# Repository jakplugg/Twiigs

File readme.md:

# Twiigs 

### 8hp dual branches.

#### PCB redesign by J. Matheson. 

it works with the same firmware, or run branches on one side, and twigs firmware on the other. all 4 inputs are normaled in a chain.

Preliminary
[Google sheets BOM](https://docs.google.com/spreadsheets/d/1JGUupowo2NgiNVYJbO-taDfZpJ7LFIUUvPUNU3bPbuE/edit#gid=1149505224)

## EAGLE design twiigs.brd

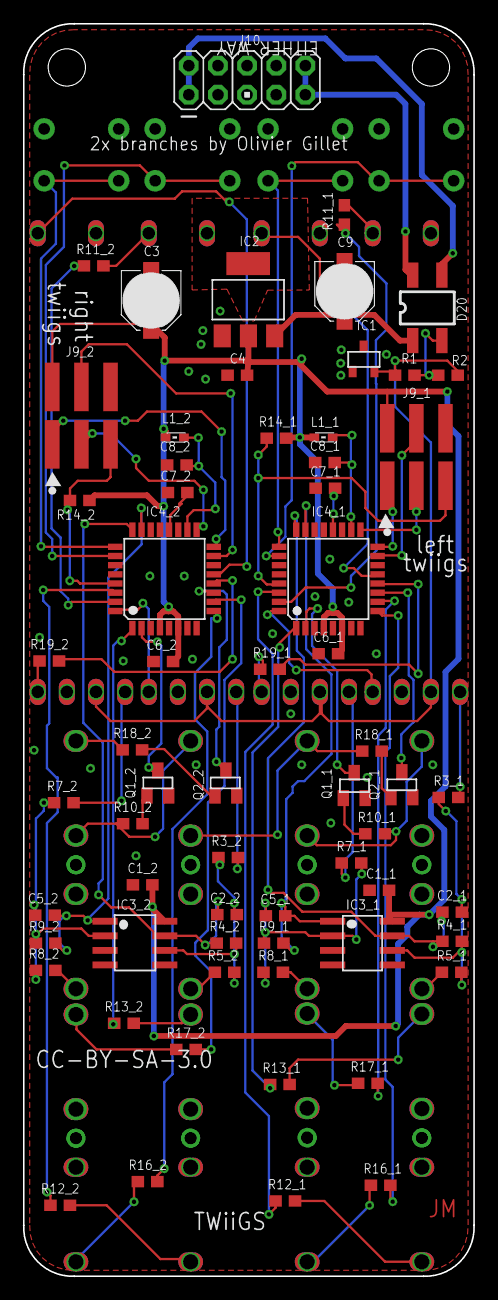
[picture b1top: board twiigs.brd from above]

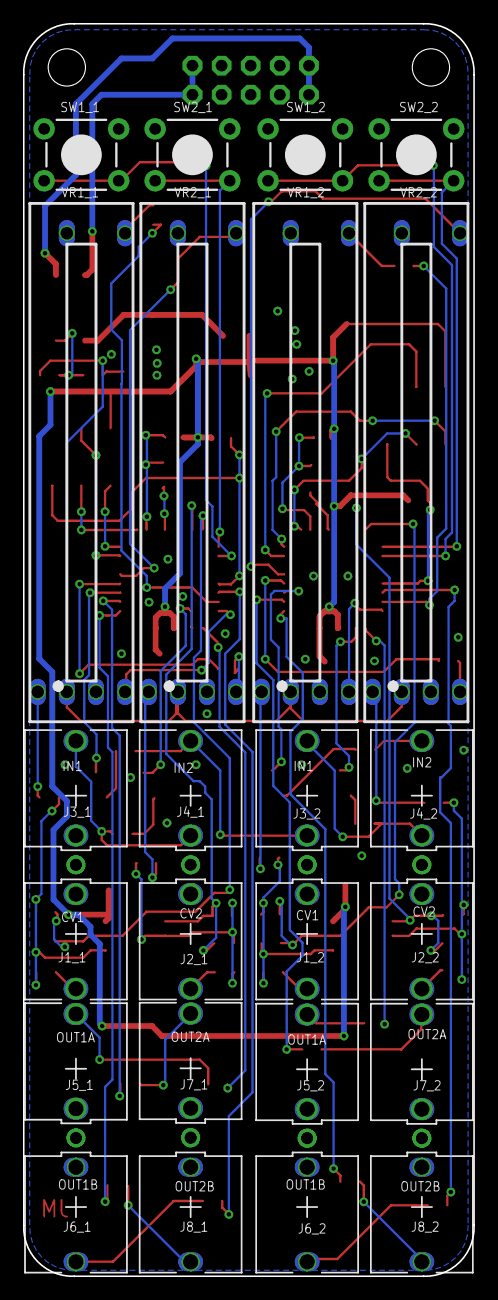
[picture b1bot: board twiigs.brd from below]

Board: 2 copper layers, 39.3 x 109.2 mm, 87 parts (24 on the bottom side), 79 nets.

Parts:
C1_1: 100n; CAP_0603_C1_1
C1_2: 100n; CAP_0603_C1_2
C2_1: 1n; CAP_0603_C2_1
C2_2: 1n; CAP_0603_C2_2
C3: 22u; PANASONIC_C
C4: 100n; CAP_0603
C5_1: 1n; CAP_0603_C5_1
C5_2: 1n; CAP_0603_C5_2
C6_1: 100n; CAP_0603_C6_1
C6_2: 100n; CAP_0603_C6_2
C7_1: 100n; CAP_0603_C7_1
C7_2: 100n; CAP_0603_C7_2
C8_1: 100n; CAP_0603_C8_1
C8_2: 100n; CAP_0603_C8_2
C9: 22u; PANASONIC_C_C9
D20: MB1S; SOP-4/6.5x2.54
IC1: LM4040 5.0V; DBZ_R-PDSO-G3
IC2: LM1117-5.0; SOT223
IC3_1: MCP6002; SO08
IC3_2: MCP6002; SO08_IC3_2
IC4_1: ATMEGA88PA-AU; TQFP32-08
IC4_2: ATMEGA88PA-AU; TQFP32-08_IC4_2
J1_1: CV1; Thonkiconn
J1_2: CV1; Thonkiconn_J1_2
J2_1: CV2; Thonkiconn_J2_1
J2_2: CV2; Thonkiconn_J2_2
J3_1: IN1; Thonkiconn_J3_1
J3_2: IN1; Thonkiconn_J3_2
J4_1: IN2; Thonkiconn_J4_1
J4_2: IN2; Thonkiconn_J4_2
J5_1: OUT1A; Thonkiconn_J5_1
J5_2: OUT1A; Thonkiconn_J5_2
J6_1: OUT1B; Thonkiconn_J6_1
J6_2: OUT1B; Thonkiconn_J6_2
J7_1: OUT2A; Thonkiconn_J7_1
J7_2: OUT2A; Thonkiconn_J7_2
J8_1: OUT2B; Thonkiconn_J8_1
J8_2: OUT2B; Thonkiconn_J8_2
J9_1: HDR-2x3S/2.54x2.54/Sh15x11
J9_2: HDR-2x3S/2.54x2.54/Sh15x11_J9_2
J10: M05X2PTH; AVR_ICSP
L1_1: 0603
L1_2: 0603_L1_2
Q1_1: MMBT3904; SOT23-BEC
Q1_2: MMBT3904; SOT23-BEC_Q1_2
Q2_1: MMBT3904; SOT23-BEC_Q2_1
Q2_2: MMBT3904; SOT23-BEC_Q2_2
R1: 3.3k; RES_0603
R2: 3.3k; RES_0603_R2
R3_1: 100k; RES_0603_R3_1
R3_2: 100k; RES_0603_R3_2
R4_1: 100k; RES_0603_R4_1
R4_2: 100k; RES_0603_R4_2
R5_1: 100k; RES_0603_R5_1
R5_2: 100k; RES_0603_R5_2
R7_1: 100k; RES_0603_R7_1
R7_2: 100k; RES_0603_R7_2
R8_1: 100k; RES_0603_R8_1
R8_2: 100k; RES_0603_R8_2
R9_1: 100k; RES_0603_R9_1
R9_2: 100k; RES_0603_R9_2
R10_1: 100k; RES_0603_R10_1
R10_2: 100k; RES_0603_R10_2
R11_1: 220; RES_0603_R11_1
R11_2: 220; RES_0603_R11_2
R12_1: 1.0k; RES_0603_R12_1
R12_2: 1.0k; RES_0603_R12_2
R13_1: 1.0k; RES_0603_R13_1
R13_2: 1.0k; RES_0603_R13_2
R14_1: 10k; RES_0603_R14_1
R14_2: 10k; RES_0603_R14_2
R16_1: 1.0k; RES_0603_R16_1
R16_2: 1.0k; RES_0603_R16_2
R17_1: 1.0k; RES_0603_R17_1
R17_2: 1.0k; RES_0603_R17_2
R18_1: 100k; RES_0603_R18_1
R18_2: 100k; RES_0603_R18_2
R19_1: 220; RES_0603_R19_1
R19_2: 220; RES_0603_R19_2
SW1_1: TACTILE-PTH
SW1_2: TACTILE-PTH_SW1_2
SW2_1: TACTILE-PTH_SW2_1
SW2_2: TACTILE-PTH_SW2_2
VR1_1: BOURNS_PTL_30mm
VR1_2: BOURNS_PTL_30mm_VR1_2
VR2_1: BOURNS_PTL_30mm_VR2_1
VR2_2: BOURNS_PTL_30mm_VR2_2

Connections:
+5V: C1_1.1, C1_2.1, C3.+, C4.1, C6_1.1, C6_2.1, IC2.2, IC3_1.8, IC3_2.8, IC4_1.4, IC4_1.6, IC4_2.4, IC4_2.6, J9_1.2, J9_2.2, L1_1.1, L1_2.1, R14_1.2, R14_2.2
AREF_1: C7_1.1, IC4_1.20
AREF_2: C7_2.1, IC4_2.20
GATE1_IN_1: J3_1.2, J4_1.1, R10_1.2
GATE1_IN_2: J3_2.2, J4_2.1, R10_2.2
GATE2_IN_2: J4_2.2, R18_2.2
GND: C1_1.2, C1_2.2, C3.-, C4.2, C6_1.2, C6_2.2, C7_1.2, C7_2.2, C8_1.2, C8_2.2, C9.-, IC1.1, IC2.1, IC3_1.3, IC3_1.4, IC3_1.5, IC3_2.3, IC3_2.4, IC3_2.5, IC4_1.3, IC4_1.5, IC4_1.21, IC4_2.3, IC4_2.5, IC4_2.21, J1_1.3, J1_2.3, J2_1.3, J2_2.3, J3_1.1, J3_1.3, J3_2.3, J4_1.3, J4_2.3, J5_1.3, J5_2.3, J6_1.3, J6_2.3, J7_1.3, J7_2.3, J8_1.3, J8_2.3, J9_1.6, J9_2.6, J10.3, J10.4, J10.5, J10.6, J10.7, J10.8, Q1_1.E, Q1_2.E, Q2_1.E, Q2_2.E, SW1_1.1, SW1_1.2, SW1_2.1, SW1_2.2, SW2_1.1, SW2_1.2, SW2_2.1, SW2_2.2, VR1_1.3, VR1_2.3, VR2_1.3, VR2_2.3
IN1_1: IC4_1.2, Q1_1.C
IN1_2: IC4_2.2, Q1_2.C
IN2_1: IC4_1.11, Q2_1.C
IN2_2: IC4_2.11, Q2_2.C
MISO_1: IC4_1.16, J9_1.1
MISO_2: IC4_2.16, J9_2.1
MOSI_1: IC4_1.15, J9_1.4
MOSI_2: IC4_2.15, J9_2.4
unnamed: Q1_1.B, R10_1.1
unnamed: Q1_2.B, R10_2.1
unnamed: Q2_1.B, R18_1.1
unnamed: Q2_2.B, R18_2.1
unnamed: C5_1.1, IC3_1.2, R7_1.2, R8_1.2, R9_1.1
unnamed: C5_2.1, IC3_2.2, R7_2.2, R8_2.2, R9_2.1
unnamed: J8_1.2, R16_1.2
unnamed: J8_2.2, R16_2.2
unnamed: R7_1.1, VR2_1.2
unnamed: R7_2.1, VR2_2.2
unnamed: R3_1.1, VR1_1.2
unnamed: R3_2.1, VR1_2.2
unnamed: J1_1.2, R5_1.1
unnamed: J1_2.2, R5_2.1
unnamed: J2_1.2, R8_1.1
unnamed: J2_2.2, R8_2.1
unnamed: IC4_1.31, R11_1.1
unnamed: IC4_2.31, R11_2.1
unnamed: R11_1.2, VR1_1.5
unnamed: R11_2.2, VR1_2.5
unnamed: IC4_1.32, VR1_1.6
unnamed: IC4_2.32, VR1_2.6
unnamed: IC4_1.13, VR2_1.5
unnamed: IC4_2.13, VR2_2.5
unnamed: R19_1.1, VR2_1.6
unnamed: R19_2.1, VR2_2.6
unnamed: IC4_1.12, R19_1.2
unnamed: IC4_2.12, R19_2.2
unnamed: C2_1.1, IC3_1.6, R3_1.2, R4_1.1, R5_1.2
unnamed: C2_2.1, IC3_2.6, R3_2.2, R4_2.1, R5_2.2
unnamed: J5_1.2, R13_1.2
unnamed: J5_2.2, R13_2.2
unnamed: J6_1.2, R12_1.2
unnamed: J6_2.2, R12_2.2
unnamed: J7_1.2, R17_1.2
unnamed: J7_2.2, R17_2.2
unnamed: C8_1.1, IC4_1.18, L1_1.2
unnamed: C8_2.1, IC4_2.18, L1_2.2
Net_0: D20.3, J10.1, J10.2
Net_43: J3_2.1, J4_1.2, R18_1.2
Net_44: D20.4, J10.9, J10.10
OUT1_A_1: IC4_1.1, R13_1.1
OUT1_A_2: IC4_2.1, R13_2.1
OUT1_B_1: IC4_1.30, R12_1.1
OUT1_B_2: IC4_2.30, R12_2.1
OUT2_A_1: IC4_1.10, R17_1.1
OUT2_A_2: IC4_2.10, R17_2.1
OUT2_B_1: IC4_1.9, R16_1.1
OUT2_B_2: IC4_2.9, R16_2.1
P1_CV_1: C2_1.2, IC3_1.7, IC4_1.24, R4_1.2
P1_CV_2: C2_2.2, IC3_2.7, IC4_2.24, R4_2.2
P2_CV_1: C5_1.2, IC3_1.1, IC4_1.23, R9_1.2
P2_CV_2: C5_2.2, IC3_2.1, IC4_2.23, R9_2.2
REF_-5: IC1.2, R1.2, R2.2, VR1_1.1, VR1_2.1, VR2_1.1, VR2_2.1
RESET_1: IC4_1.29, J9_1.5, R14_1.1
RESET_2: IC4_2.29, J9_2.5, R14_2.1
SCK_1: IC4_1.17, J9_1.3
SCK_2: IC4_2.17, J9_2.3
SW1_1: IC4_1.26, SW1_1.3, SW1_1.4
SW1_2: IC4_2.26, SW1_2.3, SW1_2.4
SW2_1: IC4_1.25, SW2_1.3, SW2_1.4
SW2_2: IC4_2.25, SW2_2.3, SW2_2.4
VCC: C9.+, D20.1, IC2.3
VEE: D20.2, R1.1, R2.1

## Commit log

2018-08-17 :boom::camel: Added .gitattributes & .gitignore files
2018-09-02 initial
    twiigs first release
2018-09-02 text
    spelling are bad!
2018-10-31 wrong url for BOM
2018-11-20 changed r1 and r2 to 3.3k
2018-11-27 removed CNC panel
2019-01-23 Panel FPD
2019-04-08 added eagle files
2019-04-08 eagle panel
2020-05-27 added ibom and swapp outs hex
2021-04-08 added original branches hex
2021-06-24 wrong ibom!

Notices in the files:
twiigs.brd:
CC-BY-SA-3.0
